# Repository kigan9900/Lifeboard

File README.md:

# Lifeboard :)

Lifeboard is a small micropad that opens apps and websites with one button press. Classroom, YouTube, ChatGPT—whatever you need, instantly. It cuts down setup time and helps you stay focused.

---

## Inspiration

I procrastinate a lot, and I waste more time than I should opening the same apps every day. So I built something that just… does it for me.

If I have something due soon, I can hit a few buttons and instantly open Classroom, ChatGPT, and YouTube. Saves a couple minutes and makes everything smoother.

---

## How it works

- Preset modes controlled by an EC11 rotary encoder (School, Chill, Hackclub, GitHub, etc.)
- One-press multi-app launching
- Small and simple enough to fit anywhere

---

## Code and Animations

This is a **surprise** for you to find once you make it, but there is a mascot and a bunch of icons!

> PS the code is in <ins>KMK</ins> because you can hot swap the binds easier, and because Python's easy

---

## Design

### *The Keys are supposed to be white*

#### Turn the encoder to switch presets. Press a button to launch whatever you assigned.

---

## Schematic

---

## PCB Layout

**PCB Design:**

**3D PCB Model:**

---

## 3D Prints

**Top view:**

**Bottom view:**

---

## Bill of Materials (BOM)

- 4× SW_Push — SW_Cherry_MX_1.00u_PCB
- 2× RotaryEncoder — RotaryEncoder_Alps_EC12E-Switch_Vertical_H20mm
- 1× OLED_128x32 — OLED_128x32
- 2× 4.7 kΩ — R_Axial_DIN0207_L6.3mm_D2.5mm_P7.62mm_Horizontal
- 1× XIAO-RP2040-SMD — XIAO-RP2040-DIP
- 4× Mounting Screws — M3x16mm

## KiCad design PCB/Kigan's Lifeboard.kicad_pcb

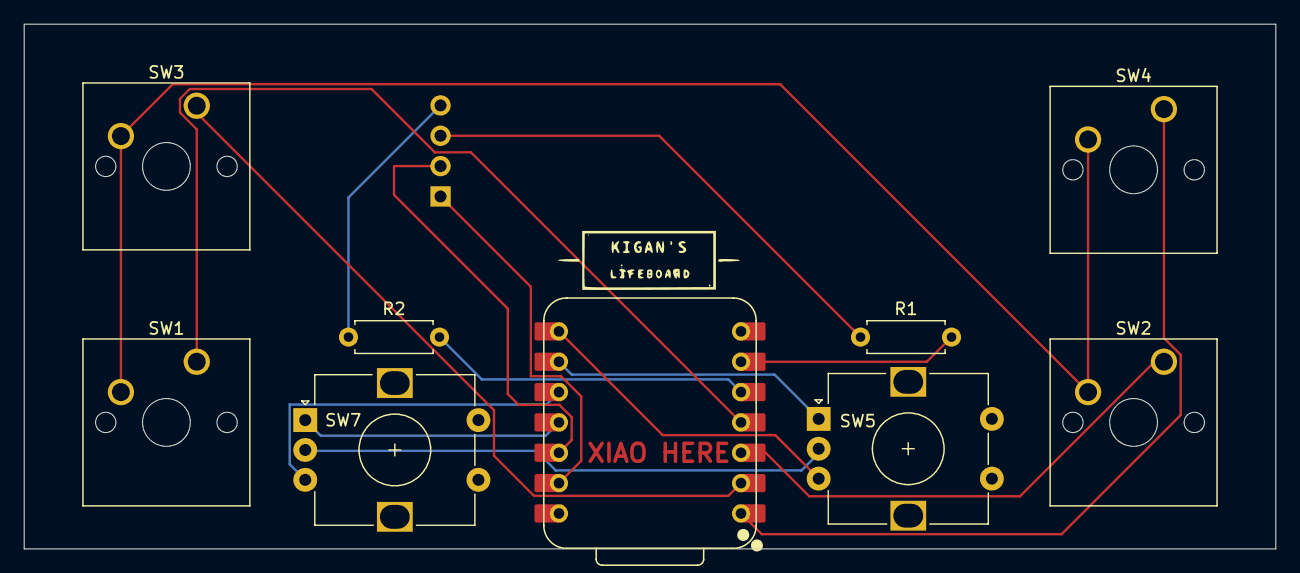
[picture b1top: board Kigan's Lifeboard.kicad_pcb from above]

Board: 2 copper layers, 104.8 x 43.9 mm, 10 parts (0 on the bottom side), 16 nets.

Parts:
J1: OLED_128x32
R1, R2: 4.7 kohm; R_Axial_DIN0207_L6.3mm_D2.5mm_P7.62mm_Horizontal
SW1, SW2, SW3, SW4: SW_Push; SW_Cherry_MX_1.00u_PCB
SW5, SW7: RotaryEncoder; RotaryEncoder_Alps_EC12E-Switch_Vertical_H20mm
U1: XIAO-RP2040-SMD; XIAO-RP2040-DIP

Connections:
GND: SW1.2, SW2.2, SW3.2, SW4.2
unnamed: J1.1 (GND), U1.13 (GND)
unnamed: J1.3 (SCL), R1.1
unnamed: J1.4 (SDA), R2.1
unnamed: J1.2 (VCC), U1.12 (3V3)
unnamed: SW5.C, SW7.C
unnamed: SW5.B, U1.8 (GPIO1_D7_CSn_RX)
unnamed: SW5.A, U1.9 (GPIO2_D8_SCK)
unnamed: SW7.A, U1.11 (GPIO3_D10_MOSI)
unnamed: SW7.B, U1.10 (GPIO4_D9_MISO)
unnamed: R2.2, U1.5 (GPIO6_D4_SDA)
unnamed: R1.2, U1.6 (GPIO7_D5_SCL)
unnamed: SW4.1, U1.1 (GPIO26_A0_D0)
unnamed: SW3.1, U1.2 (GPIO27_A1_D1)
unnamed: SW2.1, U1.3 (GPIO28_A2_D2)
unnamed: SW1.1, U1.4 (GPIO29_A3_D3)

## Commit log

2025-12-07 Create Firmware
